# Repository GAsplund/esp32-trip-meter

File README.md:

# ESP32 Trip Meter
An ESP32-based trip meter primarily made for measuring fuel efficiency.

## Background and motivation
I started this project in search of a solution for measuring the fuel efficiency on my '97 Volvo 940.
The only real solution I found prior was the [MPGuino](http://mpguino.wiseman.ee/eng), but I quickly realised it wasn't for my needs.
What I wanted was to have a solution that was as clean as possible, so having a separate display that I had to mount somewhere was out of the question.

Instead, I built it around a standard Bluetooth OBD-II interface, which would allow any device to get information and display it in any way they want.
This was perfect for my use case, as I wanted to display all the information on my phone or Android stereo via the [Torque](https://play.google.com/store/apps/details?id=org.prowl.torque) app.

## Features
- Measure fuel efficiency (L/100km)
- Measure velocity (Km/h)
- Measure fuel injection speed (L/h)
- Display data through an emulated ELM327 (OBD-II) interface

## Connections
- The negative side of the injector is connected to corresponding input on the board
  - NOTE: Must be a saturation-type injector (read below)
- A pulsed signal of the vehicle speed sensor (VSS) is connected to VSS+
  - Variable reluctance (VR) speed sensors do not seem to work

### Power and ground
The ground reference and power is currently given by the USB port on the ESP32.
This may change later due to being a limiting factor.

## Injector types
This project is mainly made to support saturation-type injectors.
If your engine uses other types of injectors, such as peak-and-hold injectors, this project **will not work**.

The easiest way to check this is to measure the resistance of an injector;
If it has a resistance of around 12Ω, it is a saturation-type injector.
If it has a resistance of around 2-3Ω, it is likely a **peak-and-hold** injector.

**Also note that** injectors that are connected for batch injection may be connected in parallel, and may in some cases display a resistance that is lower than normal.

The reason why peak-and-hold injectors will not work, is that they work differently from saturation injectors.
While saturation injectors simply open while the signal is active, a peak-and-hold injector, like its name suggests, sends a high voltage signal which forces the injector open (peak).
After that, a lower-voltage signal (normally around 12 volts) is pulsed through the remainder of the opening time (hold).

## Platform compatibility
Since the project currently uses ESP32-specific platform code a lot, it would be difficult to port to using normal Arduino implementations.
It may be possible to port it to ESP8266 devices, but they would need a discrete Bluetooth module.

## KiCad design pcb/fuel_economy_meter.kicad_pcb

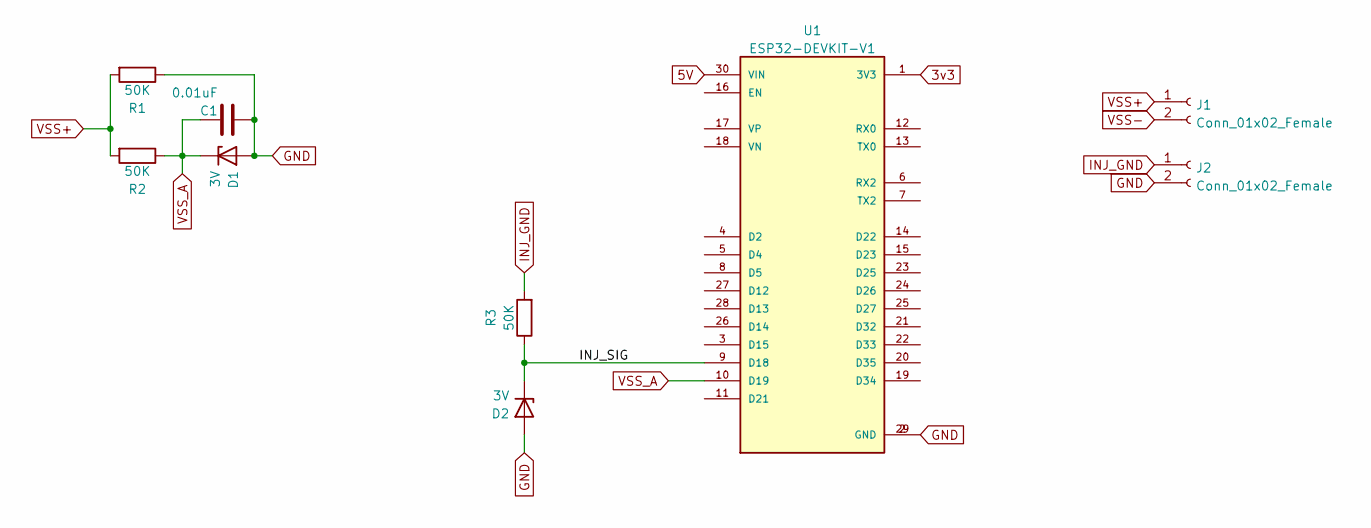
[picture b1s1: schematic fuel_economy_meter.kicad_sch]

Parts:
C1: 0.01uF; C_1206_3216Metric_Pad1.33x1.80mm_HandSolder
D1, D2: 3V; D_SOD-123
J1, J2: Conn_01x02_Female; JST_XH_B2B-XH-A_1x02_P2.50mm_Vertical
R1, R2, R3: 50K; R_1206_3216Metric_Pad1.30x1.75mm_HandSolder
U1: ESP32-DEVKIT-V1; MODULE_ESP32_DEVKIT_V1; PARTREV N/A

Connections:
3v3: U1.1 (3V3)
5V: U1.30 (VIN)
/INJ_SIG: D2.1 (K), R3.1, U1.9 (D18)
GND: C1.2, D1.2 (A), D2.2 (A), J2.2, R1.1, U1.2 (GND), U1.29 (GND)
INJ_GND: J2.1, R3.2
VSS+: J1.1, R1.2, R2.2
VSS-: J1.2
VSS_A: C1.1, D1.1 (K), R2.1, U1.10 (D19)

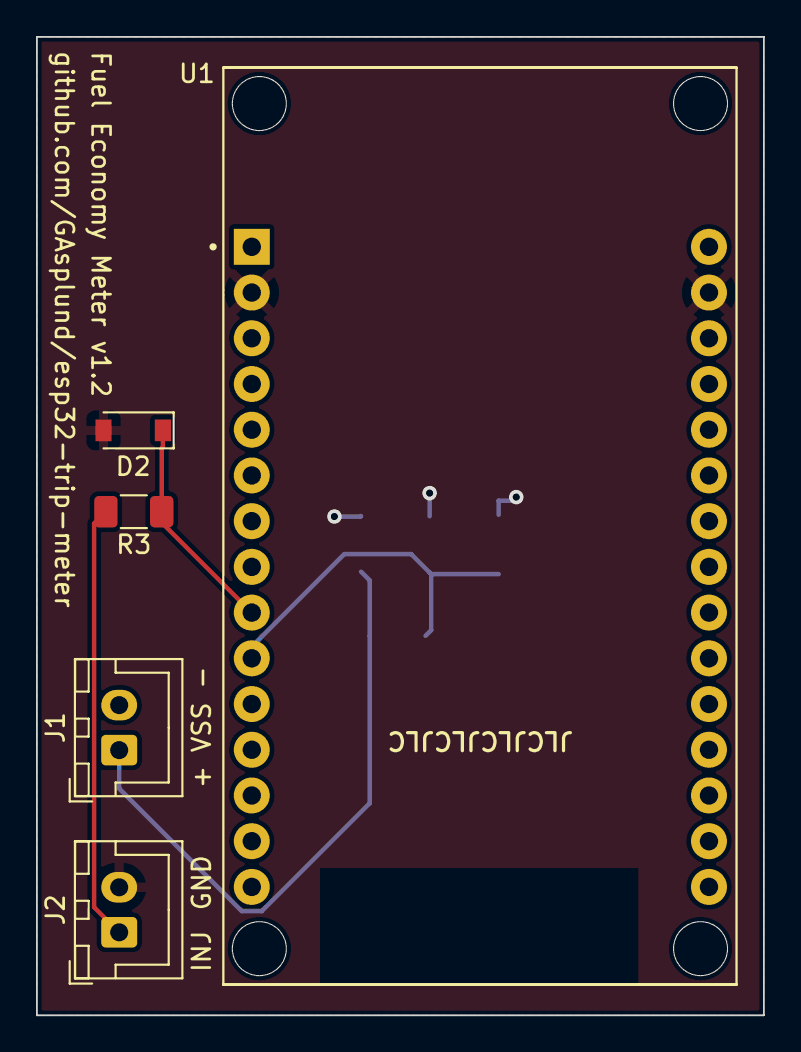
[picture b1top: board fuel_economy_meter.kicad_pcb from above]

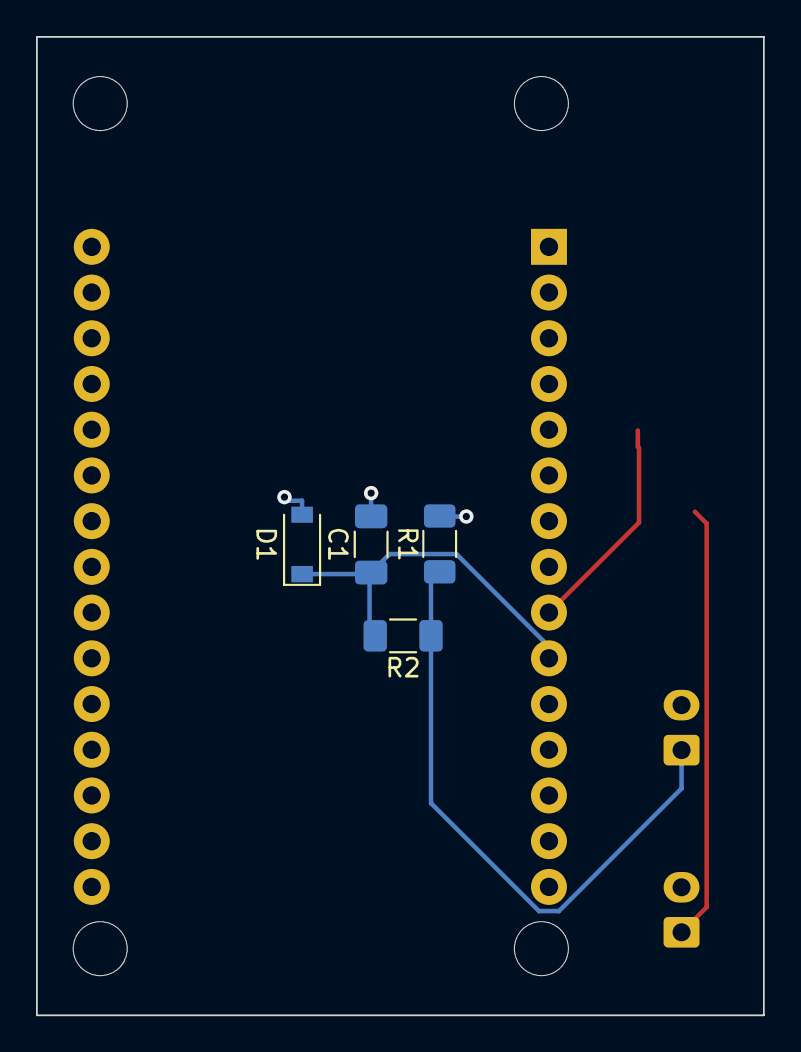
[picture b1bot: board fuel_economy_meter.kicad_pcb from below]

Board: 2 copper layers, 40.4 x 54.4 mm, 9 parts (4 on the bottom side), 5 nets.

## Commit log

2023-07-12 Import project
2023-07-12 Add a readme with some info
2023-07-12 More info
2023-07-15 Fix compilation issues related to header files
2023-07-16 Define Trip class functions properly
2023-07-16 Consolidate config variables into one file
2023-07-16 Remove unnecessary class declaration
2023-08-02 Remove VR sensor circuit
2023-08-05 Formatting, get velocity from signal period
    ISR functions are now based on the latest instantiated Trip class
2023-08-05 Add missing this
2023-08-05 Better naming
2023-08-05 Calculate total trip properly, fix ISR arguments
2023-08-05 Add docs to Trip class
2023-08-07 Add discrete ELM327 and log classes
2023-08-07 Docs with Doxygen
2023-08-07 Correct indentation
2023-08-07 Correct file name
2023-08-07 Remove extra s
2023-08-07 Proper cache restore paths
2023-08-07 Oops
2023-08-07 Initialize ISR on begin instead of constructor
2023-08-07 Calculate momentary consumption rates
2023-09-17 Sample time immediately on interrupt
2023-09-17 Clearer documentation
2023-09-17 Use MCPWM, velocity and injector timeouts
2023-09-17 Remove extra comment
2023-09-17 Convert timer ticks to microseconds
2023-09-27 Renaming and better comments
2023-10-22 Fix watchdog timeouts in ISRs, correct timer config
2023-10-23 Correct VSS MCPWM unit, attempt to fix overflow
2023-10-23 Better ELM327 compat
2023-10-24 Don't use strapping pin for injector signal
2023-10-27 Explicit types, avoid float division
    This shaves off a good amount of CPU cycles here and there.
    Since the ESP32 FPU doesn't have division, this is done in software.
    GCC doesn't simplify division by a constant into multiplication
    without using flags, so multiplication is done explicitly in code
    where possible.
    Also specifying a floating point value implicitly makes it double
2023-10-30 Consolidate component designators
2023-10-30 EEPROM class
2023-12-18 Remove C++ files
2023-12-18 Create Rust project
2023-12-18 Add untested frequency counter
2023-12-18 Add untested ELM327 emulator
2024-03-31 Use MCPWM capture module
    commit 8dee15fa3eb3471cc0f6acbb4060af64bcf9d584
    Author: Goostaf <gasplund2@gmail.com>
    Date: Mon Apr 1 00:22:32 2024 +0200
    Use pullup for VSS
    commit 28c861ac5c9a93706a4724ec72dc9858fb7a0068
    Author: Goostaf <gasplund2@gmail.com>
